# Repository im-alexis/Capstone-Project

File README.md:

# Capstone Project
# Autonomous Plant Watering System Senior Design

Faculty Mentor: Dr. Wei Li

Team Members: Javier Padilla, Alexis Torres, Ian Skillman, Kiet Le, Evan LeBel, Jesus Hernandez, Jaime Sanchez, Rodrigo Romero

Project Description:
Due to changes in the weather and busy work weeks, it can be challenging to keep track of when you last watered your plants. Our Watering System will automate the need to keep track of the last time you watered your plants and give you more time to enjoy seeing your plants grow. This can create longevity in plants including flowers and plants that can feed humans for years to come. 
Specifically, the project will focus on a single unit that contains a small to medium-sized plant. Attached to the unit will be multiple sensors that will detect/measure/record moisture, temperature, humidity, sunlight, and the water level of an in-unit source. Using a Web UI, the user will be able to manually control and set custom watering settings for the unit. 

Team Composition
4 software engineers developing the software that will use algorithms to automate the watering system based on conditions received from the sensors. All of which can be monitored and manually activated on a remote Web UI. 
3 embedded systems engineers working on communication between sensors and microcontroller, as well as any drivers necessary for the attached LCD display or features that are going to be added. Adding additional electronics to power the microcontroller (including a battery pack and solar cell)

Objectives
Embedded Systems Development: Efficient and reliable embedded systems that control hardware components and devices.
Firmware and Software Development: Creating software and firmware to control and interact with hardware components, creating communication with full functionality.
Networking and Communication: Designing systems that can communicate with each other using various communication protocols (TCP or UDP), such as Wi-Fi or Bluetooth.
Test and Validation: Develop test plans and methodologies to ensure that the designed systems and components meet performance and reliability requirements.
Usability and User Experience: Design software interfaces that are user-friendly experience for end-users.
Scalability and Performance: Build software that can handle increased user loads and data info while maintaining optimal performance.
Compatibility: Develop software that is compatible with multiple devices, operating systems, and browsers, to ensure consistent user experience across platforms.
Code Reviews: Collaborative code reviews to maintain code quality, pass knowledge, and resolve code-related issues.
Documentation: Create comprehensive documentation to outline software functionality, architecture, APIs, and usage guidelines.
Data Management: Design a robust data management system to ensure data integrity for software data storage and processing.
Teams
Embedded Systems Team:

Members: Ian Skillman, Evan LeBel, and Jaime Sanchez
Subsystems: Plant Microcontroller, Hub, Wireless, PCB Design
Roles: Firmware/Software, PCB Designer, Hardware Test/Validation, RF, Power, and Data Packet design
Members: 
Ian     - Sensors communication and plant Micro and Water Mechanics
	Evan  - Plant info and Water Mechanics/System Designer/HUB Master/PCB design
	Jaime - Communications/PCB design
Team Timeline:
Checkpoint 1: APIs - TBD
Checkpoint 2: Plant Microcontroller  - TBD
Checkpoint 3: Hub Microcontroller - TBD
Checkpoint 4: Plant-Hub Communication - TBD 
Checkpoint 5: Water Mechanics Design  - TBD
Checkpoint 6: Custom PCB Schematics - TBD 
Checkpoint 7: Final Casing/Housing - TBD

Design Idea:
A plant module will have 3 attached sensors: Light, moisture, and temperature. These sensors will communicate with a custom PCB where the microcontroller will be located. Each plant will have its own sensors and microcontroller, but can also be expanded to accommodate multiple plants per microcontroller. The microcontroller will periodically read the sensors and, based on the sensor data, enable or disable a water pump that delivers water into the plant's soil. The water flow will be fixed, with the amount of water released determined by a time-based factor. The water pump will be connected to a water tank equipped with a sensor to monitor the water level within the tank. This sensor will communicate with the hub, which will be responsible for broadcasting notifications regarding the need to refill the tank. Each microcontroller will communicate with the hub via Bluetooth to periodically send current sensor readings from the plants. The hub can receive multiple data packets from various microcontrollers. Bluetooth will utilize the TCP protocol to prevent interference. The hub will then relay the received data packets over Wi-Fi to be accessed by the PC user for reading and analysis.

Demonstrations of multiple Plant modules per tank/HUB

Software Team: Web Development

Members: Alexis Torres, Kiet Le, Javier Padilla, and Jesus Hernandez
Subsystems: Server / UI - Backend/Front End
Roles:
	Front End Dev: Alexis Torres and Javier Padilla
	Backend Dev: Kiet Le and Jesus Hernandez
Description:
The software team's primary responsibility involves developing the web application, which serves as the user interface for the project. This entails creating a comprehensive, full-stack application capable of storing both user and plant data. Additionally, the software team will manage the critical communication link between the user and the microcontroller.

To ensure a seamless user experience, the team will focus on crafting an intuitive and user-friendly interface, accompanied by an aesthetically pleasing user interface design.

Requirements: 
User Friendly UI
Dark/Light Mode
Language Setting
English
Spanish
Etc.
Account System
Admin Level Control
System Customization
Manual Control
Adding and Configuring Plant Profile
Standard User Level
Monitoring 
Monitoring
Graphical Sensor Data Display
Water Level
Light Detection
Moisture Level
Etc.
System Settings Customization
Custom Plant Profiles
Water Needs
Lights Needs
Data Transmission Rate
New Plant Integration
History
Saving Packets Received from the system
Maintaining History of Notification Events / System Events
Notifications 
SMS
Email
Upscale:
App Development:
Convert the web app into a mobile app that can be accessed on both IOS and Android. 
System Design Draft:
<INPUT PROJECT NAME>
Project Description: <NEEDS WORK>

Team Composition
4 software engineers developing the software that will use algorithms to automate the watering system based on conditions received from the sensors. All of which can be monitored and manually activated on a remote Web UI. 
3 embedded systems engineers working on communication between sensors and microcontroller, as well as any drivers necessary for the attached LCD display or features that are going to be added. Adding additional electronics to power the microcontroller (including a battery pack and solar cell)
Objectives <Fill in Data>
Teams
Embedded Systems Team: <NEED WORK>

Members: Ian Skillman, Evan LeBel, and Jaime Sanchez
Subsystems: Plant Microcontroller, Hub, Wireless, PCB Design
Roles: Firmware/Software, PCB Designer, Hardware Test/Validation, RF, Power, and Data Packet design
Members: 
Ian     - 
	Evan  - 
	Jaime - 
Team Timeline:
Software Team: Web Development

Members: Alexis Torres, Kiet Le, Javier Padilla, and Jesus Hernandez
Subsystems: Server / UI - Backend/Front End
Roles:
	Front End Dev: Alexis Torres and Javier Padilla
	Backend Dev: Kiet Le and Jesus Hernandez
Description:
The software team's primary responsibility involves developing the web application, which shall function as a tool for doctors to monitor patient’s health. This entails creating a comprehensive, full-stack application capable of storing both user and sensor data. Additionally, the software team will manage the critical communication link between the user and the microcontroller. 

To ensure a seamless user experience, the team will focus on crafting an intuitive and user-friendly interface, accompanied by an aesthetically pleasing user interface design.

The goal is to set a framework for health monitoring, where more wearable devices can interface with the web application.  

Requirements: 
User Friendly UI
Dark/Light Mode
Language Setting
English
Spanish
Etc.
Account System
Admin/ Doctor Level Control
System Customization
Manual Control
Adding and Configuring Patient Profile
Standard User Level
Monitoring their own device data
Monitoring
Graphical Sensor Data Display

Etc.
System Settings Customization
Data Transmission Rate
New device integration
History
Saving Packets Received from the system
Maintaining History of Notification Events / System Events
Notifications 
SMS
Email

Upscale:
App Development:
Convert the web app into a mobile app that can be accessed on both IOS and Android. 
Interface for health monitoring wearable devices

System Design Draft:

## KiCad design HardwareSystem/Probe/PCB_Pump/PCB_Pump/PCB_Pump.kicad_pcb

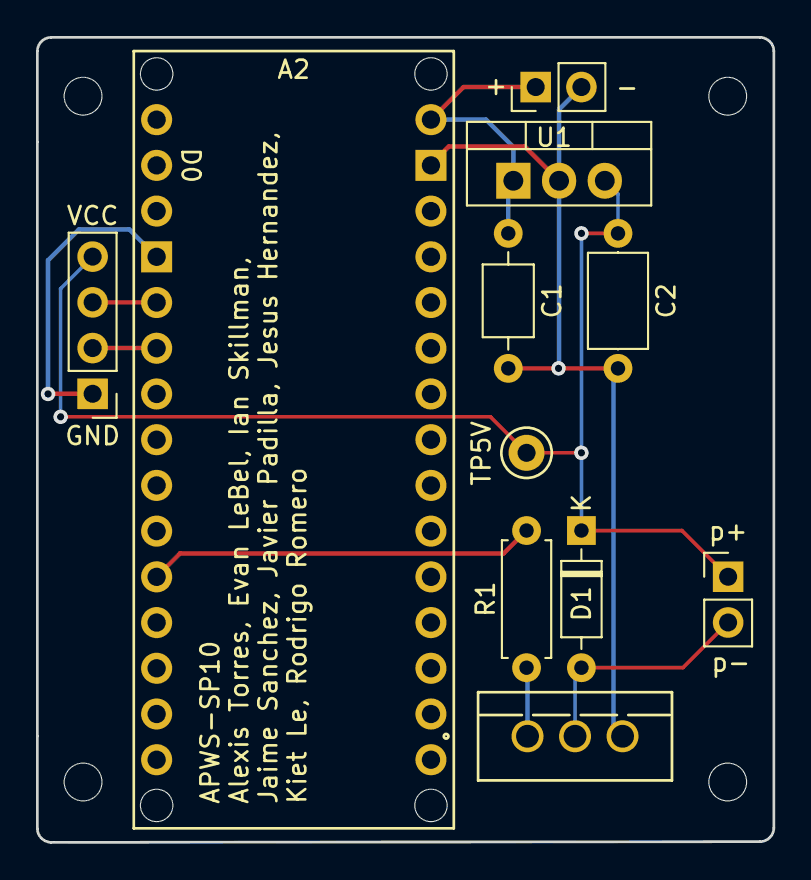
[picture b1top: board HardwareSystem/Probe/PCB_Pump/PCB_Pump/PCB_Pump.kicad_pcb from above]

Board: 2 copper layers, 40.9 x 44.7 mm, 11 parts (0 on the bottom side), 8 nets.

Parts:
+: PinHeader_1x02_P2.54mm_Vertical
A2: Arduino_Nano_ESP32_Socket
C1: 0.1 uF; C_Axial_L3.8mm_D2.6mm_P7.50mm_Horizontal
C2: 10 uF; C_Axial_L5.1mm_D3.1mm_P7.50mm_Horizontal
D1: 1N914; D_DO-35_SOD27_P7.62mm_Horizontal
GND: Conn_01x04_Pin; PinHeader_1x04_P2.54mm_Vertical
Q1: IRF510; IRF510PBF
R1: 12k; R_Axial_DIN0207_L6.3mm_D2.5mm_P7.62mm_Horizontal
TP5V: TestPoint_Keystone_5000-5004_Miniature
U1: LM2937xT; TO-220-3_Vertical
p+: PinHeader_1x02_P2.54mm_Vertical

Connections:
9V: +.1, A2.VIN, C1.1, U1.1 (VI)
Echo: A2.D3, GND.2
GND: +.2, A2.GND1 (GND), A2.GND2 (GND), C1.2, C2.2, GND.1, Q1.3 (S), U1.2 (GND)
unnamed: A2.D8, R1.1
unnamed: Q1.1 (G), R1.2
Trig: A2.D2, GND.3
pump+: C2.1, D1.1 (K), GND.4, TP5V.1, U1.3 (VO), p+.1
pump-: D1.2 (A), Q1.2 (D), p+.2

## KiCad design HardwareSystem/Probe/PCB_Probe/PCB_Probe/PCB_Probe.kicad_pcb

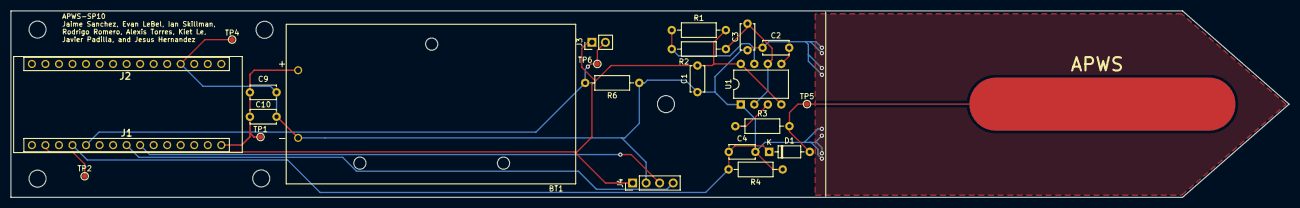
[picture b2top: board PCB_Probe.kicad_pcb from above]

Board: 2 copper layers, 240.0 x 35.0 mm, 28 parts (0 on the bottom side), 12 nets.

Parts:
BT1: BH9VPC; BAT_BH9VPC
C1, C9, C10: 100nF; C_Disc_D4.7mm_W2.5mm_P5.00mm
C2: 10nF; C_Disc_D4.7mm_W2.5mm_P5.00mm
C3: 470pF; C_Disc_D4.7mm_W2.5mm_P5.00mm
C4: 10uF; C_Disc_D4.7mm_W2.5mm_P5.00mm
D1: 1N4148; D_DO-35_SOD27_P7.62mm_Horizontal
H1, H2, H3, H4, H5: MountingHole; MountingHole_3.2mm_M3
J1, J2: Conn_01x15; PRT16279
J3: Conn_01x02_Socket; PinHeader_1x02_P2.54mm_Vertical
J4: Conn_01x04_Pin; PinHeader_1x04_P2.54mm_Vertical
R1: 330R; R_Axial_DIN0207_L6.3mm_D2.5mm_P10.16mm_Horizontal
R2: 1.6kR; R_Axial_DIN0207_L6.3mm_D2.5mm_P10.16mm_Horizontal
R3, R6: 10kR; R_Axial_DIN0207_L6.3mm_D2.5mm_P10.16mm_Horizontal
R4: 1MF; R_Axial_DIN0207_L6.3mm_D2.5mm_P10.16mm_Horizontal
TP1: 9V Testpoint; TestPoint_Pad_D1.0mm
TP2: 3.3V Testpoint; TestPoint_Pad_D1.0mm
TP4: 3.3V GND Testpoint; TestPoint_Pad_D1.0mm
TP5: Mouisture Testpoint; TestPoint_Pad_D1.0mm
TP6: Light Testpoint; TestPoint_Pad_D1.0mm
U1: TLC555xP; DIP-8_W7.62mm

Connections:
+3.3V: C1.2, J1.2, J3.1, J4.1, R1.1, TP2.1, U1.4 (R), U1.8 (VCC)
+9V: BT1.+, C9.1, C10.1, J1.15, TP1.1
A_Light: J1.5, J3.2, R6.2, TP6.1
A_Moisture: C4.1, D1.1 (K), J1.4, R4.2
GND: BT1.-, C1.1, C2.2, C3.1, C4.2, C9.2, C10.2, J2.12, J4.2, R4.1, R6.1, TP4.1, U1.1 (GND)
unnamed: C2.1, U1.5 (CV)
unnamed: R1.2, R2.2, U1.7 (DIS)
unnamed: R3.1, U1.3 (Q)
unnamed: C3.2, R2.1, U1.2 (TR), U1.6 (THR)
Probe: D1.2 (A), R3.2, TP5.1
SCL: J1.9, J4.3
SDA: J1.8, J4.4

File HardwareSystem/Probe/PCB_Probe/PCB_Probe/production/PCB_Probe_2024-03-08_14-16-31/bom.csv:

Designator,Footprint,Quantity,Value,LCSC Part #
BT1,BAT_BH9VPC,1,BH9VPC,
"C1, C10, C9",C_Disc_D4.7mm_W2.5mm_P5.00mm,3,100nF,
C2,C_Disc_D4.7mm_W2.5mm_P5.00mm,1,10nF,
C3,C_Disc_D4.7mm_W2.5mm_P5.00mm,1,470pF,
C4,C_Disc_D4.7mm_W2.5mm_P5.00mm,1,10uF,
D1,D_DO-35_SOD27_P7.62mm_Horizontal,1,1N4148,
"H1, H2, H3, H4, H5",MountingHole_3.2mm_M3,5,MountingHole,
"J1, J2",PRT16279,2,Conn_01x15,
J3,PinHeader_1x02_P2.54mm_Vertical,1,Conn_01x02_Socket,
J4,PinHeader_1x04_P2.54mm_Vertical,1,Conn_01x04_Pin,
R1,R_Axial_DIN0207_L6.3mm_D2.5mm_P10.16mm_Horizontal,1,330R,
R2,R_Axial_DIN0207_L6.3mm_D2.5mm_P10.16mm_Horizontal,1,1.6kR,
"R3, R6",R_Axial_DIN0207_L6.3mm_D2.5mm_P10.16mm_Horizontal,2,10kR,
R4,R_Axial_DIN0207_L6.3mm_D2.5mm_P10.16mm_Horizontal,1,1MF,
TP1,TestPoint_Pad_D1.0mm,1,9V Testpoint,
TP2,TestPoint_Pad_D1.0mm,1,3.3V Testpoint,
TP4,TestPoint_Pad_D1.0mm,1,3.3V GND Testpoint,
TP5,TestPoint_Pad_D1.0mm,1,Mouisture Testpoint,
TP6,TestPoint_Pad_D1.0mm,1,Light Testpoint,
U1,DIP-8_W7.62mm,1,TLC555xP,

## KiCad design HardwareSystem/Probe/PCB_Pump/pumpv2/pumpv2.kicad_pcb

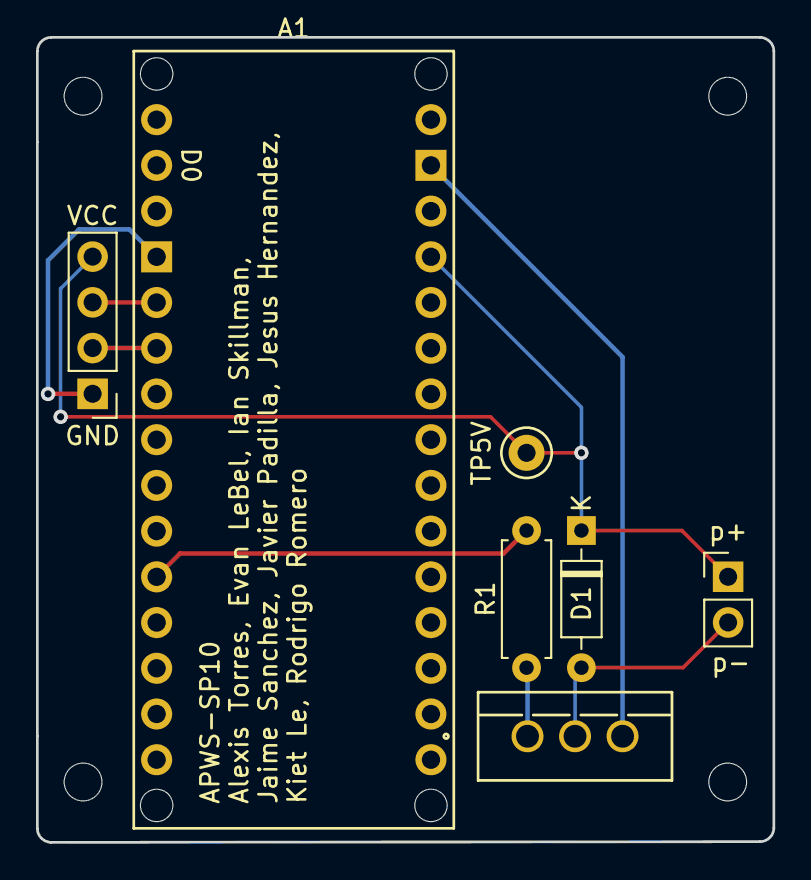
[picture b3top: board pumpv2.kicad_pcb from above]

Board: 2 copper layers, 40.9 x 44.7 mm, 7 parts (0 on the bottom side), 5 nets.

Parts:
A1: Arduino_Nano_ESP32_Socket
D1: 1N914; D_DO-35_SOD27_P7.62mm_Horizontal
GND: Conn_01x04_Pin; PinHeader_1x04_P2.54mm_Vertical
Q1: IRF510; IRF510PBF
R1: 12k; R_Axial_DIN0207_L6.3mm_D2.5mm_P7.62mm_Horizontal
TP5V: TestPoint_Keystone_5000-5004_Miniature
p+: PinHeader_1x02_P2.54mm_Vertical

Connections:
GND: A1.GND1 (GND), A1.GND2 (GND), Q1.3 (S)
unnamed: A1.D8, R1.1
unnamed: Q1.1 (G), R1.2
pump+: A1.5V, D1.1 (K)
pump-: D1.2 (A), Q1.2 (D)

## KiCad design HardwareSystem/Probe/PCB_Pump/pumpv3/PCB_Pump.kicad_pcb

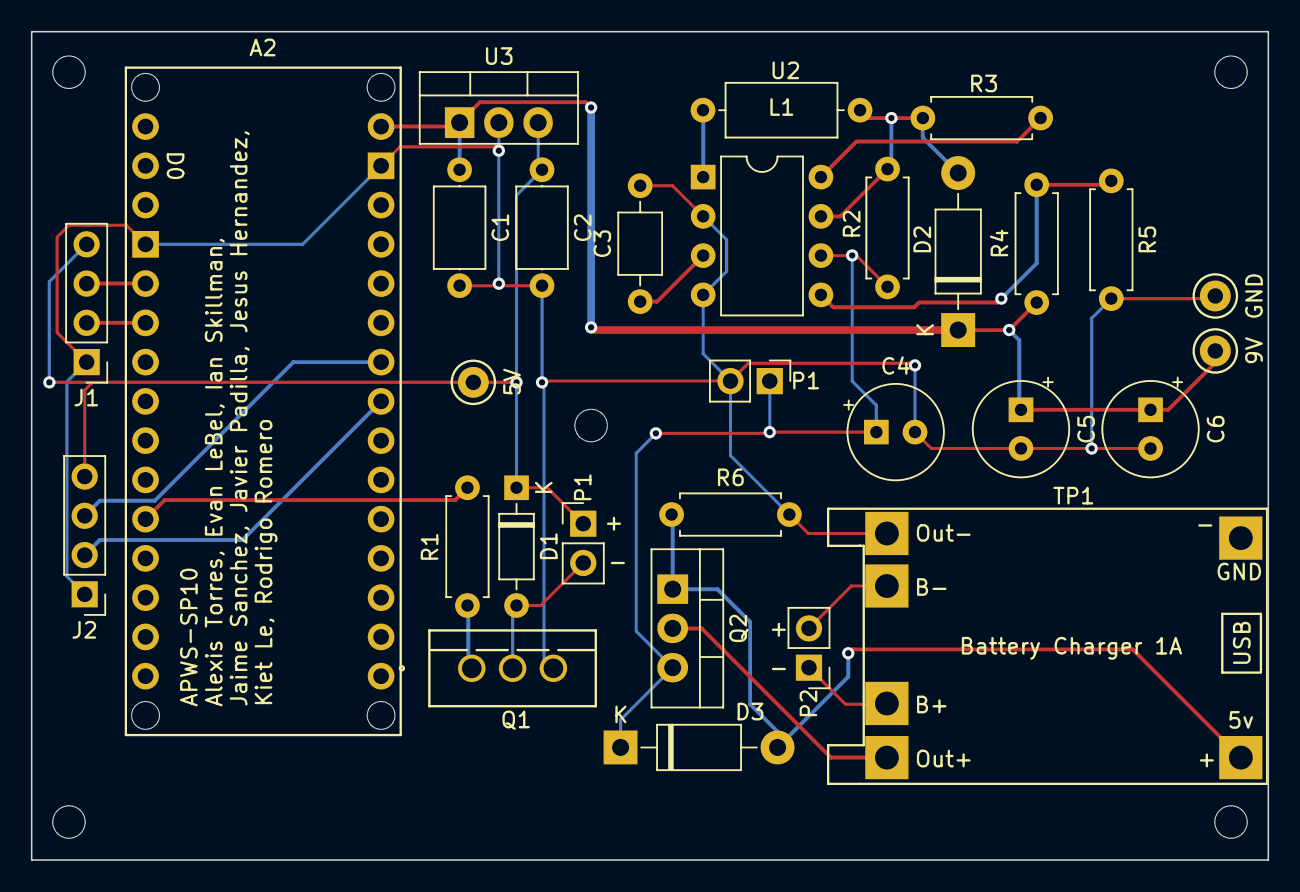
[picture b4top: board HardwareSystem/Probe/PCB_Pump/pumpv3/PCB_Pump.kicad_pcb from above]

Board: 2 copper layers, 80.0 x 53.6 mm, 30 parts (0 on the bottom side), 20 nets.

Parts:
5V, 9V: TestPoint_Keystone_5000-5004_Miniature
A2: Arduino_Nano_ESP32_Socket
C1: 0.22 uF; C_Axial_L5.1mm_D3.1mm_P7.50mm_Horizontal
C2: 0.1 uF; C_Axial_L5.1mm_D3.1mm_P7.50mm_Horizontal
C3: 1nF; C_Axial_L3.8mm_D2.6mm_P7.50mm_Horizontal
C4, C5, C6: 100uF; CP_Radial_Tantal_D6.0mm_P2.50mm
D1: 1N914; D_DO-35_SOD27_P7.62mm_Horizontal
D2: 1N5819; D_DO-41_SOD81_P10.16mm_Horizontal
D3: 1N5817; D_DO-41_SOD81_P10.16mm_Horizontal
GND: TestPoint_Keystone_5000-5004_Miniature
J1, J2: Conn_01x04_Pin; PinHeader_1x04_P2.54mm_Vertical
L1: 1000uH; L_Axial_L7.0mm_D3.3mm_P10.16mm_Horizontal_Fastron_MICC
P1, P1#2, P2: PinHeader_1x02_P2.54mm_Vertical
Q1: IRF510; IRF510PBF
Q2: IRF4905; TO-220-3_Vertical
R1: 12k; R_Axial_DIN0207_L6.3mm_D2.5mm_P7.62mm_Horizontal
R2: 0.22; R_Axial_DIN0207_L6.3mm_D2.5mm_P7.62mm_Horizontal
R3: 180; R_Axial_DIN0207_L6.3mm_D2.5mm_P7.62mm_Horizontal
R4: 6.2K; R_Axial_DIN0207_L6.3mm_D2.5mm_P7.62mm_Horizontal
R5: 1k; R_Axial_DIN0207_L6.3mm_D2.5mm_P7.62mm_Horizontal
R6: 10K; R_Axial_DIN0207_L6.3mm_D2.5mm_P7.62mm_Horizontal
TP1: TP4056; TP4056-18650
U2: MC33063AP; DIP-8_W7.62mm
U3: LM7805_TO220; TO-220-3_Vertical

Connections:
3V7+: C4.1, D3.1 (K), P1#2.1, Q2.3 (S), R2.2, U2.6 (Vin)
3V7-: A2.GND1 (GND), A2.GND2 (GND), C1.2, C2.2, C3.2, C4.2, C5.2, C6.2, GND.1, J1.1, J2.1, P1#2.2, Q1.3 (S), R5.2, R6.2, TP1.4 (out-), U2.2 (SwE), U2.4 (GND), U3.2 (GND)
9V: 9V.1, A2.VIN, C1.1, C5.1, C6.1, D2.1 (K), R4.1, U3.1 (VI)
Batt+: P2.1, TP1.5 (B+)
Batt-: P2.2, TP1.6 (B-)
Echo: A2.D3, J1.2
unnamed: A2.D8, R1.1
unnamed: D2.2 (A), L1.1, R2.1, R3.2, U2.7 (Ipk)
unnamed: D3.2 (A), Q2.1 (G), R6.1, TP1.1 (in+)
unnamed: Q1.1 (G), R1.2
unnamed: Q2.2 (D), TP1.3 (out+)
unnamed: R3.1, U2.8 (DC)
unnamed: L1.2, U2.1 (SwC)
unnamed: C3.1, U2.3 (TC)
P5: R4.2, R5.1, U2.5 (Vfb)
SCL: A2.A5 (A5/SCL), J2.3
SDA: A2.A4 (A4/SDA), J2.2
Trig: A2.D2, J1.3
pump+: 5V.1, C2.1, D1.1 (K), J1.4, J2.4, P1.1, U3.3 (VO)
pump-: D1.2 (A), P1.2, Q1.2 (D)

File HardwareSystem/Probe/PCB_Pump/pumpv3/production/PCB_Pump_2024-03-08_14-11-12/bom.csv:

Designator,Footprint,Quantity,Value,LCSC Part #
"5V, 9V, GND",TestPoint_Keystone_5000-5004_Miniature,3,TestPoint_Keystone_5000-5004_Miniature,
A2,Arduino_Nano_ESP32_Socket,1,Arduino_Nano_ESP32_Socket,
C1,C_Axial_L5.1mm_D3.1mm_P7.50mm_Horizontal,1,0.22 uF,
C2,C_Axial_L5.1mm_D3.1mm_P7.50mm_Horizontal,1,0.1 uF,
C3,C_Axial_L3.8mm_D2.6mm_P7.50mm_Horizontal,1,1nF,
"C4, C5, C6",CP_Radial_Tantal_D6.0mm_P2.50mm,3,100uF,
D1,D_DO-35_SOD27_P7.62mm_Horizontal,1,1N914,
D2,D_DO-41_SOD81_P10.16mm_Horizontal,1,1N5819,
D3,D_DO-41_SOD81_P10.16mm_Horizontal,1,1N5817,
"J1, J2",PinHeader_1x04_P2.54mm_Vertical,2,Conn_01x04_Pin,
L1,L_Axial_L7.0mm_D3.3mm_P10.16mm_Horizontal_Fastron_MICC,1,1000uH,
"P1_2, P1, P2",PinHeader_1x02_P2.54mm_Vertical,3,PinHeader_1x02_P2.54mm_Vertical,
Q1,IRF510PBF,1,IRF510,
Q2,TO-220-3_Vertical,1,IRF4905,
R1,R_Axial_DIN0207_L6.3mm_D2.5mm_P7.62mm_Horizontal,1,12k,
R2,R_Axial_DIN0207_L6.3mm_D2.5mm_P7.62mm_Horizontal,1,0.22,
R3,R_Axial_DIN0207_L6.3mm_D2.5mm_P7.62mm_Horizontal,1,180,
R4,R_Axial_DIN0207_L6.3mm_D2.5mm_P7.62mm_Horizontal,1,6.2K,
R5,R_Axial_DIN0207_L6.3mm_D2.5mm_P7.62mm_Horizontal,1,1k,
R6,R_Axial_DIN0207_L6.3mm_D2.5mm_P7.62mm_Horizontal,1,10K,
TP1,TP4056-18650,1,TP4056,
U2,DIP-8_W7.62mm,1,MC33063AP,
U3,TO-220-3_Vertical,1,LM7805_TO220,

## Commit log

2023-09-19 File Organization Templete
2023-09-19 File Organization Templete adjusted
2024-02-06 created react application
2024-02-06 added login and create-user page
2024-02-15 Skeleton of Flask App, Virtual Env Instrusctions
2024-02-16 Login Page Style Edits (MAJOR WORK IN PROGRESS)
2024-02-19 Removed Vines in login square
2024-02-19 Added More JS Files For WebPages
2024-02-19 Create Hub
    Creating files
2024-02-19 Create Probe
    Creating files
2024-02-24 Added testing sensor testing files and probe kicad proj
    Files added:
    ATH20 Sessor code,
    Capacitive moisture sensor,
    Initial Kicad PCB project for probe
2024-02-26 Added Incomplete login functionality in login.js file
2024-02-26 All Sensors in one Arduino File
2024-02-26 Progress on CreateUser and Forgot JS Files
2024-02-28 Forgot Password Page Created (No Functional Actions)
2024-02-28 file repath
2024-02-28 PCB probe WIP
2024-02-28 pump pcb
2024-02-28 Route Templete, File Orgainzation
2024-02-28 Login Progress (Syncing/Login Button/User Type)
2024-02-28 Login Func written and seem functional
2024-02-29 Added more circuits to PCB probe
    Added more circuits to PCB probe
2024-02-29 Renamed Server.py -> app.py. And Made Changes In app.py To Test Login Functionality
2024-02-29 Adjustments to mongo client
2024-02-29 Merge
2024-02-29 added access field for json reponse to route "/"
2024-03-01 more layout design
    Added:
    header footprint
    pcb margins for probe
2024-03-02 PCB Probe layout
    working on pcb probe layout
2024-03-02 pump pcb work
2024-03-02 esp32 model
2024-03-02 Routing and Placement for Probe PCB
2024-03-03 finished PCB pump
2024-03-04 Register System Function Seems Functional
2024-03-04 Create & Login Functionality Ready For Testing
2024-03-04 pcb pump revision
2024-03-04 dashboard initial layout (still needs styling)
2024-03-04 Adjustment on request reception
2024-03-04 Login/Create Progress
2024-03-04 updated Probe schematic look
2024-03-05 Cleaned Up Login and CreateUser files
2024-03-05 modified dashboard and added plant card component
2024-03-05 made upgrades to dashboard styling and functionality
2024-03-06 added functionality to join button for demo purposes
2024-03-06 updated ground plane footprint
2024-03-07 Updated the requirements.txt
2024-03-07 git ignore update for virtual environment
2024-03-07 removed redundant 3V LDO
2024-03-08 pumpv2-v3
2024-03-08 pumpv3-added some symbols
2024-03-08 updates on both boards
2024-03-21 templete for data reception from HW, update to requirements.txt
2024-03-25 Updated app.py
2024-03-26 MessageFunction Updated In Backend
2024-03-27 Messaging Update
2024-03-27 API route for user sending join request is functional/Tested
2024-03-28 backend Test Folder
2024-03-28 SystemFunctions.py added
2024-03-28 Communication
2024-03-28 Join Request/Akn Request Is functional
2024-03-29 Leave System and System Info api are functional, adjustments to system registration
2024-03-29 COMMUNICATION WORKS DUB
2024-03-29 Communication works Hardware Side
2024-03-29 Function Optimization, tested works as before
2024-03-29 Adjustments
2024-03-29 File Renaming and Reorganization of Functions
2024-03-30 Can change roles/ and remove user, updated akn request to consider role
2024-03-31 Sending Emails is Partially Setup
2024-03-31 Login Style Changes
2024-03-31 Progrss on Password Reset
2024-04-01 Reset Password Progress
2024-04-03 OTP Setup in Testing
2024-04-04 Created All OTP/Reset Functions In The Server
2024-04-04 Added Comments
2024-04-05 Errors in Forget Password
2024-04-05 battery level example code
2024-04-05 Battery Level sensor and testing bluetooth stuff
2024-04-09 OTP Verification Works For Forget Password (reset still WIP)
2024-04-09 User can now recieve invites from a system
2024-04-09 System Invite Akn, working
2024-04-10 OTP/Email Verification Completed
2024-04-10 changed buck wiring
2024-04-10 Incomplete Reset Password Setup
2024-04-10 added landing page, but still incomplete
2024-04-11 added landing page to routes
2024-04-11 created history page
2024-04-11 fixed bugs
2024-04-11 Added Recieving Http stuff, no idea if it works
2024-04-11 fixed some comments i screwed up
2024-04-11 Recieve from server
2024-04-11 3d models
2024-04-11 Exapansion of HW interaction, sys_user_invite bug fix, ground work for noti and sys_users func, file reformatting
2024-04-11 Postman Templetes in test folder
2024-04-11 Update values depending on get from server
2024-04-11 route for a watering button is been set up
2024-04-11 Accounting for unregistered device and advancing states
2024-04-11 added Login button to home page
2024-04-12 made some changes to homescreen landing page
2024-04-12 Finished homepage, sorta
2024-04-12 fixed link rerouting
2024-04-12 new bottom hub 3d model
2024-04-12 "/" route renamed to "/login",
2024-04-12 modified team section on landing page
2024-04-12 fixed images on homepage
2024-04-12 Bug fix
2024-04-12 Streamlining code
2024-04-12 Small changes
2024-04-14 updated 3d model
2024-04-15 dashboard online - Javier
2024-04-17 /dashboard fix, was not returning correct thing, NEW DATABASE FORMATTING
2024-04-18 Changed login & forgot to .jsx files
2024-04-18 Converted Verify.js into jsx
2024-04-19 Testing Reset Password
2024-04-22 Reset Password Works
2024-04-22 register system now works, also added session storage functionaluty to store if a user is logged in
2024-04-22 join_ system Functionality works
2024-04-22 Comments
2024-04-22 dashboard accuratly dsiplays data
2024-04-23 Converted CreateUser to JSX file
2024-04-23 Working On Removing Plants
2024-04-23 changed naming of dashboard to a jsx file
2024-04-23 fixed styling
2024-04-23 minor mods
2024-04-24 fixed styling further
2024-04-24 more styling changes
2024-04-24 Added custom sys_name capabilities and some limiter for the water route
2024-04-25 New setting parameter pumpActiveLength is available
2024-04-25 Progress On Joining Function
2024-04-25 Developed Plant Settings (Button On Dashboard Doesn't Work Yet)
2024-04-25 added tank height requirement to registering a system
2024-04-25 fixed minor bug in register system
2024-04-25 battery_level data point, new settings param,
2024-04-25 fixed homepage pictures
2024-04-25 Plant Settings Page (Partially Works)
2024-04-25 more changes to home page
2024-04-25 more homepage updates
2024-04-25 Testing worked
2024-04-26 testing deploy branch
2024-04-26 testing
2024-04-26 Reverting back changes for deployemt, going to isolate
2024-04-26 HIstory is now working
2024-04-28 Fixed Plant Setting's Styling
2024-04-28 Landing Page Changes
2024-04-28 Login Pages' Style Changes
2024-04-28 Battery Measurmenet Update
2024-04-29 Join/Register/Dashboard/PlantSetting Style Changes
2024-04-29 Fixed Plant Photo on Dashboard
2024-04-29 Battery Life Reading On Dashboard
2024-04-29 Added Water Button
